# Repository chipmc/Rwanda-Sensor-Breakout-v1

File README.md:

# Rwanda-Sensor-Breakout-v1
 Allows for the conntection of solenoids and 5V sensors

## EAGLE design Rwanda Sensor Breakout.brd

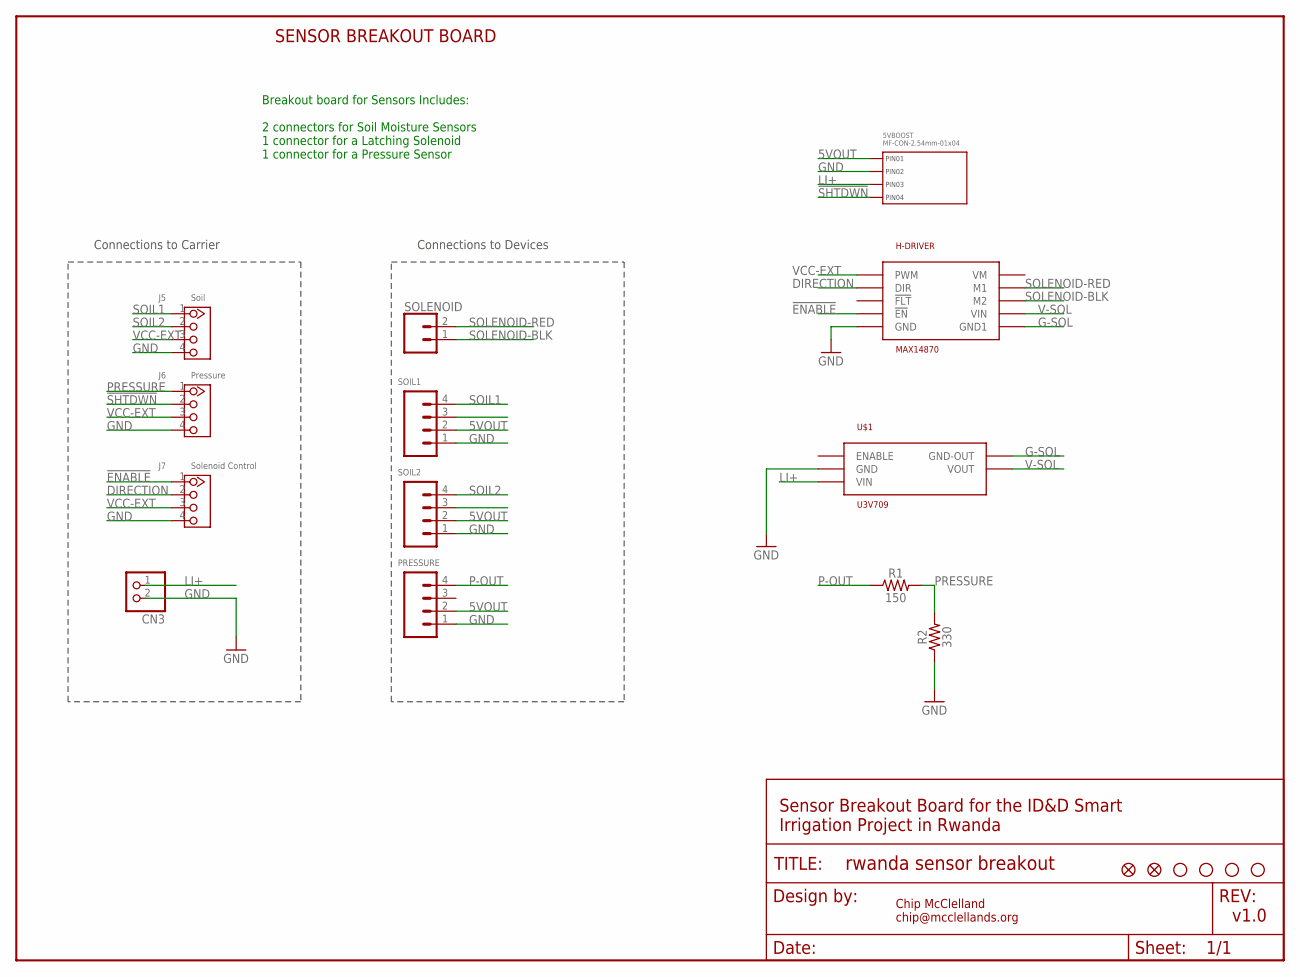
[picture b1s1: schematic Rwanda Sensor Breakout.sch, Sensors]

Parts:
5VBOOST: MF-CON-2.54mm-01x04; PTH_2.54MM_01X04
CN3: JST_2PIN-SMT-RA; JST-PH-2-SMT-RA
FD1, FD2: FIDUCIALUFIDUCIAL; FIDUCIAL-MICRO
FRAME1: FRAME-LETTER; CREATIVE_COMMONS
H-DRIVER: MAX14870; MAX14870-BREAKOUT
J5: Soil; HW4-2.0
J6: Pressure; HW4-2.0
J7: Solenoid Control; HW4-2.0
JP3, JP4, JP5, JP6: STAND-OFF
PRESSURE: Soil; SCREWTERMINAL-3.5MM-4
R1: 150; 0805
R2: 330; 0805
SOIL1, SOIL2: Soil; SCREWTERMINAL-3.5MM-4
SOLENOID: CONN_025MM; SCREWTERMINAL-5MM-2
U$1: U3V709; U3V70X-BREAKOUT

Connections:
5VOUT: 5VBOOST.P$1 (PIN1), PRESSURE.2, SOIL1.2, SOIL2.2
!ENABLE: H-DRIVER.P$4 (!EN), J7.1
!SHTDWN: 5VBOOST.P$4 (PIN4), J6.2
DIRECTION: H-DRIVER.P$2 (DIR), J7.2
G-SOL: H-DRIVER.P$6 (GND1), U$1.GOUT (GND-OUT), U$1.GOUT1 (GND-OUT)
GND: 5VBOOST.P$2 (PIN2), CN3.2 (1), H-DRIVER.P$5 (GND), J5.4, J6.4, J7.4, PRESSURE.1, R2.1, SOIL1.1, SOIL2.1, U$1.GIN (GND), U$1.GIN1 (GND)
LI+: 5VBOOST.P$3 (PIN3), CN3.1 (2), U$1.VIN, U$1.VIN1 (VIN)
P-OUT: PRESSURE.4, R1.1
PRESSURE: J6.1, R1.2, R2.2
SOIL1: J5.1, SOIL1.4
SOIL2: J5.2, SOIL2.4
SOLENOID-BLK: H-DRIVER.P$8 (M2), SOLENOID.1
SOLENOID-RED: H-DRIVER.P$9 (M1), SOLENOID.2
V-SOL: H-DRIVER.P$7 (VIN), U$1.VOUT, U$1.VOUT1 (VOUT)
VCC-EXT: H-DRIVER.P$1 (PWM), J5.3, J6.3, J7.3

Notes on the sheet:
Chip McClelland chip@mcclellands.org
v1.0
SENSOR BREAKOUT BOARD
Sensor Breakout Board for the ID&D Smart Irrigation Project in Rwanda
Breakout board for Sensors Includes: 2 connectors for Soil Moisture Sensors 1 connector for a Latching Solenoid 1 connector for a Pressure Sensor
Connections to Carrier
Connections to Devices

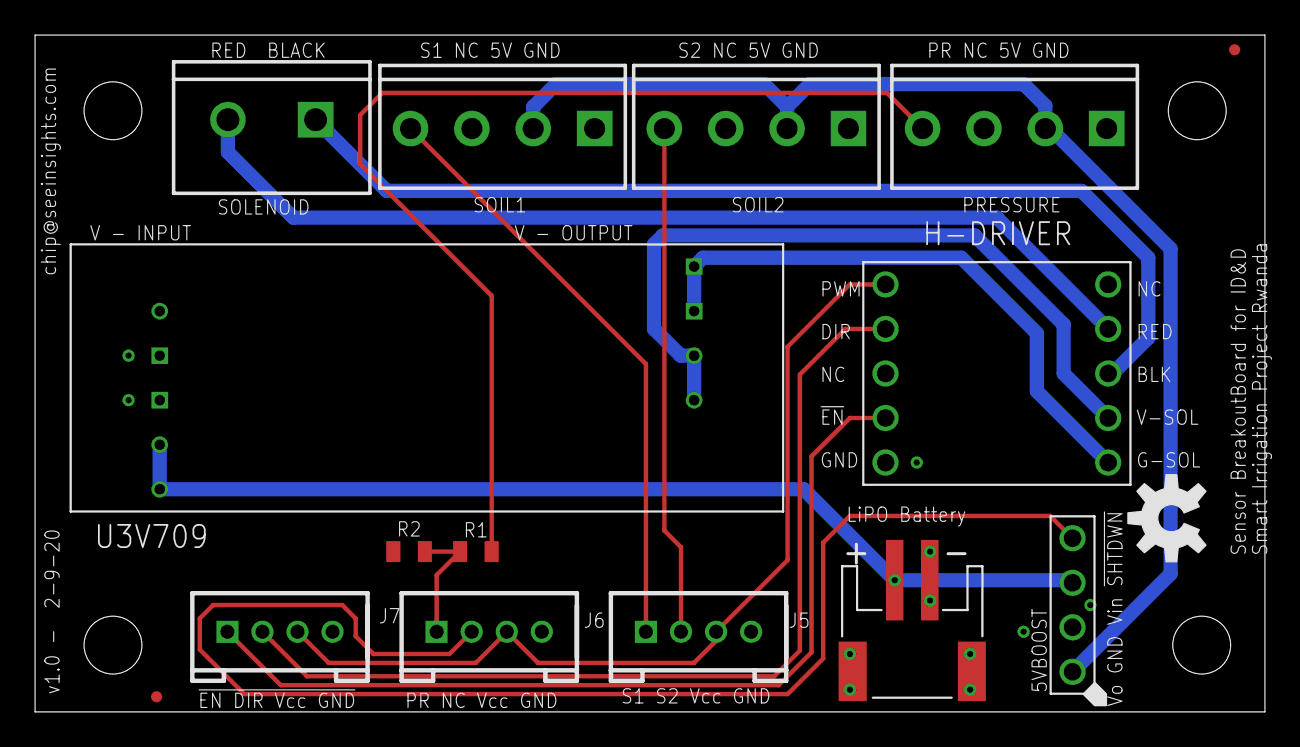
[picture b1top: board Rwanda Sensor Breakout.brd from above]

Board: 2 copper layers, 70.2 x 38.6 mm, 21 parts (0 on the bottom side), 15 nets.

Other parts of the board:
U$2: OSHW-LOGO-M

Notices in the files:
parts and their libraries:
SparkFun-Aesthetics: Licensing: Creative Commons ShareAlike 4.0 International - https://creativecommons.org/licenses/by-sa/4.0
SparkFun-Aesthetics: Released under the Creative Commons Attribution Share-Alike 4.0 License
SparkFun-Aesthetics: https://creativecommons.org/licenses/by-sa/4.0
